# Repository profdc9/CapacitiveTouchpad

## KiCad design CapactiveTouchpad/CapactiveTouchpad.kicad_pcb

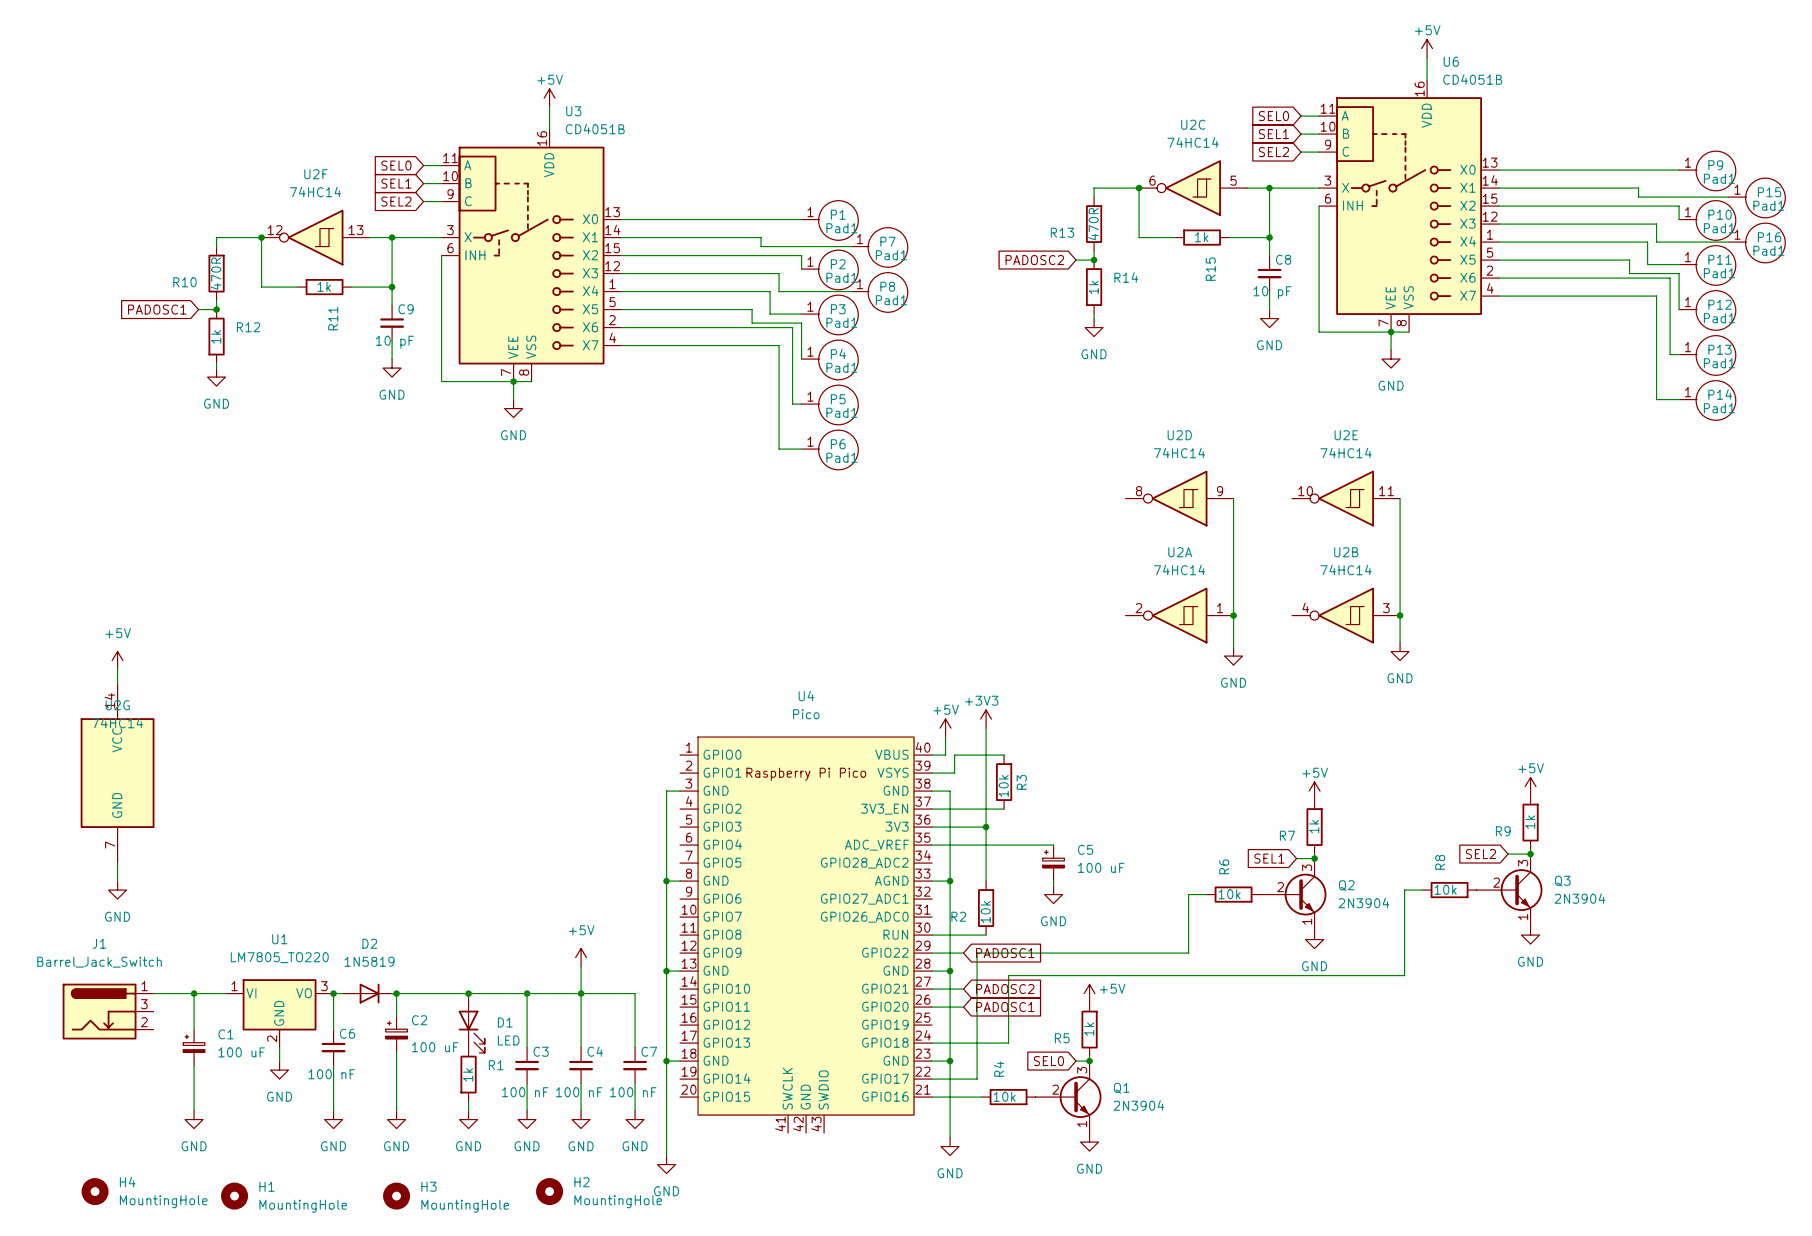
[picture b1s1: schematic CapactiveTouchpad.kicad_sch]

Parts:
C1, C2, C5: 100 uF; CP_Radial_D5.0mm_P2.50mm
C3, C4, C6, C7: 100 nF; C_Disc_D5.0mm_W2.5mm_P5.00mm
C8, C9: 10 pF; C_Disc_D5.0mm_W2.5mm_P5.00mm
D1: LED; LED_D5.0mm
D2: 1N5819; D_DO-41_SOD81_P7.62mm_Horizontal
H1, H2, H3, H4: MountingHole; MountingHole_3.2mm_M3
J1: Barrel_Jack_Switch; BarrelJack_Horizontal
P1, P2, P3, P4, P5, P6, P7, P8, P9, P10, P11, P12, P13, P14, P15, P16: Pad1; CapacitivePad1
Q1, Q2, Q3: 2N3904; TO-92_Inline_Wide
R1, R5, R7, R9, R11, R12, R14, R15: 1k; R_Axial_DIN0207_L6.3mm_D2.5mm_P7.62mm_Horizontal
R2, R3, R4, R6, R8: 10k; R_Axial_DIN0207_L6.3mm_D2.5mm_P7.62mm_Horizontal
R10, R13: 470R; R_Axial_DIN0207_L6.3mm_D2.5mm_P7.62mm_Horizontal
U1: LM7805_TO220; TO-220-3_Vertical
U2: 74HC14; DIP-14_W7.62mm_Socket
U3, U6: CD4051B; DIP-16_W7.62mm_Socket
U4: Pico; RPi_Pico_SMD_TH

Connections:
+3V3: R2.2, U4.36 (3V3)
+5V: C2.1, C3.1, C4.1, C7.1, D1.2 (A), D2.1 (K), R5.2, R7.2, R9.2, U2.14 (VCC), U3.16 (VDD), U4.40 (VBUS), U6.16 (VDD)
GND: C1.2, C2.2, C3.2, C4.2, C5.2, C6.2, C7.2, C8.2, C9.2, Q1.1 (E), Q2.1 (E), Q3.1 (E), R1.2, R12.2, R14.2, U1.2 (GND), U2.1, U2.3, U2.7 (GND), U2.9, U2.11, U3.6 (INH), U3.7 (VEE), U3.8 (VSS), U4.3 (GND), U4.8 (GND), U4.13 (GND), U4.18 (GND), U4.23 (GND), U4.28 (GND), U4.33 (AGND), U4.38 (GND), U6.6 (INH), U6.7 (VEE), U6.8 (VSS)
unnamed: C1.1, J1.1, U1.1 (VI)
unnamed: C5.1, U4.35 (ADC_VREF)
unnamed: C6.1, D2.2 (A), U1.3 (VO)
unnamed: C8.1, R15.1, U2.5, U6.3 (X)
unnamed: C9.1, R11.1, U2.13, U3.3 (X)
unnamed: D1.1 (K), R1.1
unnamed: P9.1, U6.13 (X0)
unnamed: P10.1, U6.15 (X2)
unnamed: P11.1, U6.1 (X4)
unnamed: P12.1, U6.5 (X5)
unnamed: P13.1, U6.2 (X6)
unnamed: P14.1, U6.4 (X7)
unnamed: P15.1, U6.14 (X1)
unnamed: P16.1, U6.12 (X3)
unnamed: Q1.2 (B), R4.2
unnamed: Q2.2 (B), R6.2
unnamed: Q3.2 (B), R8.2
unnamed: R2.1, U4.30 (RUN)
unnamed: R3.1, U4.37 (3V3_EN)
unnamed: R3.2, U4.39 (VSYS)
unnamed: R4.1, U4.21 (GPIO16)
unnamed: R6.1, U4.22 (GPIO17)
unnamed: R8.1, U4.24 (GPIO18)
unnamed: R10.2, R11.2, U2.12
unnamed: R13.2, R15.2, U2.6
unnamed: P3.1, U3.1 (X4)
unnamed: P5.1, U3.2 (X6)
unnamed: P6.1, U3.4 (X7)
unnamed: P4.1, U3.5 (X5)
unnamed: P8.1, U3.12 (X3)
unnamed: P1.1, U3.13 (X0)
unnamed: P7.1, U3.14 (X1)
unnamed: P2.1, U3.15 (X2)
PADOSC1: R10.1, R12.1, U4.26 (GPIO20), U4.29 (GPIO22)
PADOSC2: R13.1, R14.1, U4.27 (GPIO21)
SEL0: Q1.3 (C), R5.1, U3.11 (A), U6.11 (A)
SEL1: Q2.3 (C), R7.1, U3.10 (B), U6.10 (B)
SEL2: Q3.3 (C), R9.1, U3.9 (C), U6.9 (C)

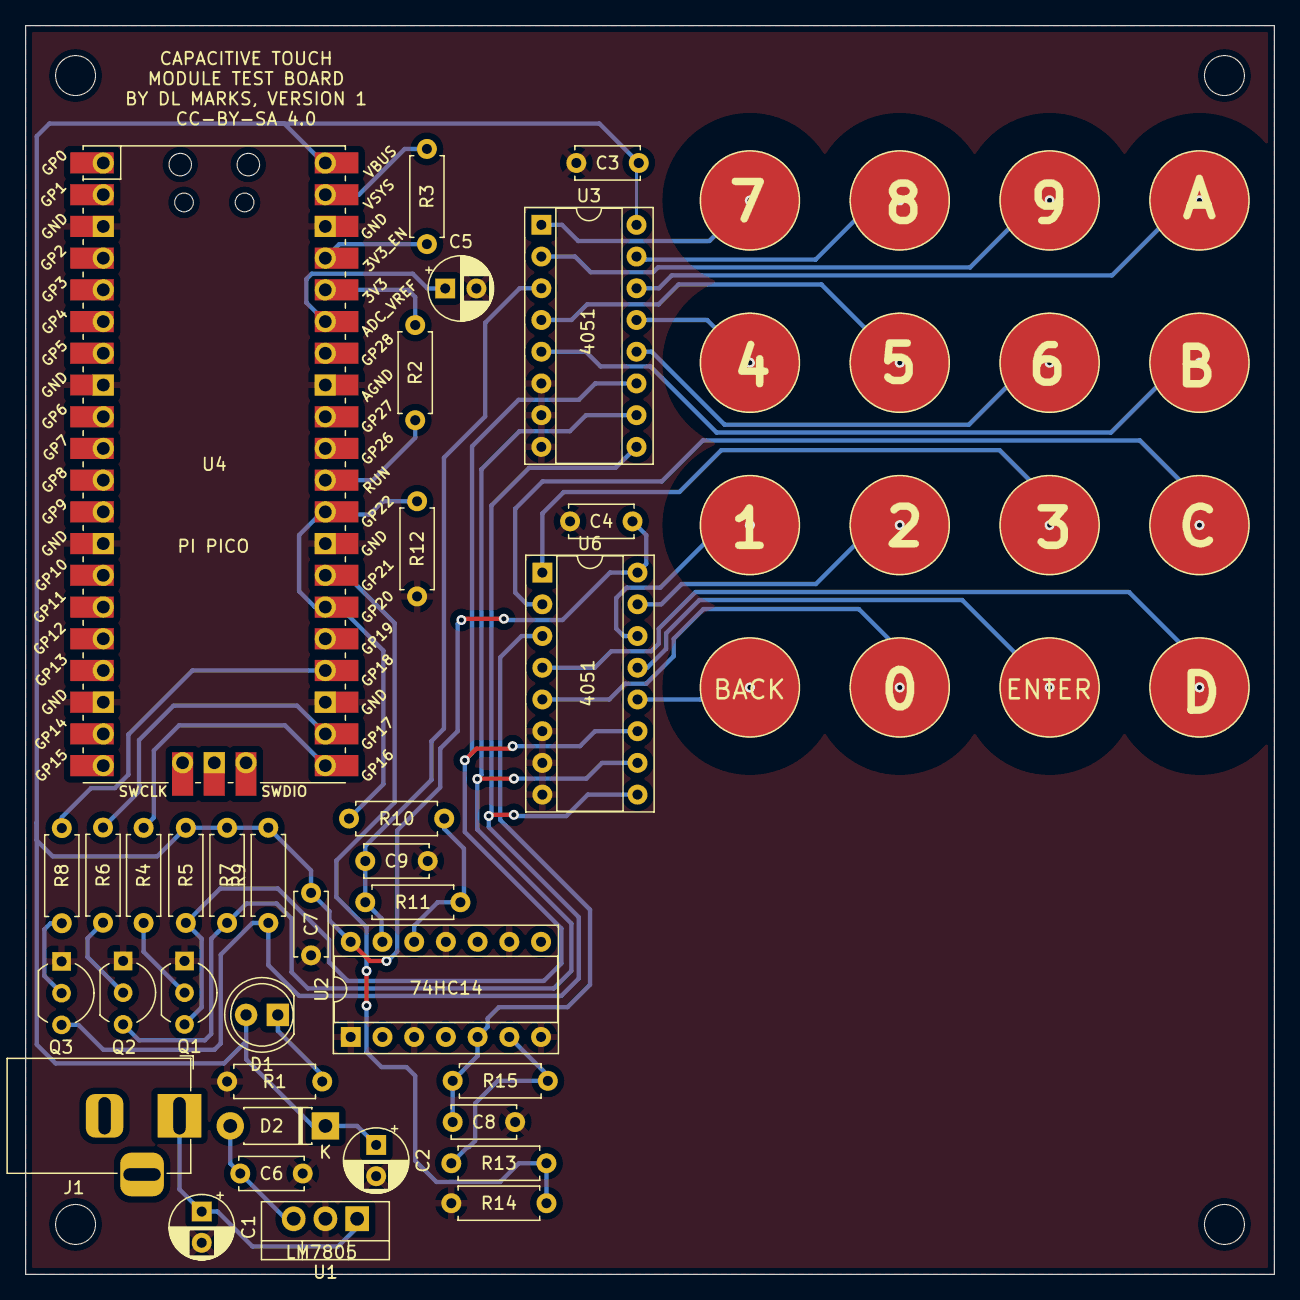
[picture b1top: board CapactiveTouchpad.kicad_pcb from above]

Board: 2 copper layers, 100.0 x 100.0 mm, 55 parts (0 on the bottom side), 41 nets.

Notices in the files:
CapactiveTouchpad/CapactiveTouchpad.kicad_pcb:
CC-BY-SA 4.0
